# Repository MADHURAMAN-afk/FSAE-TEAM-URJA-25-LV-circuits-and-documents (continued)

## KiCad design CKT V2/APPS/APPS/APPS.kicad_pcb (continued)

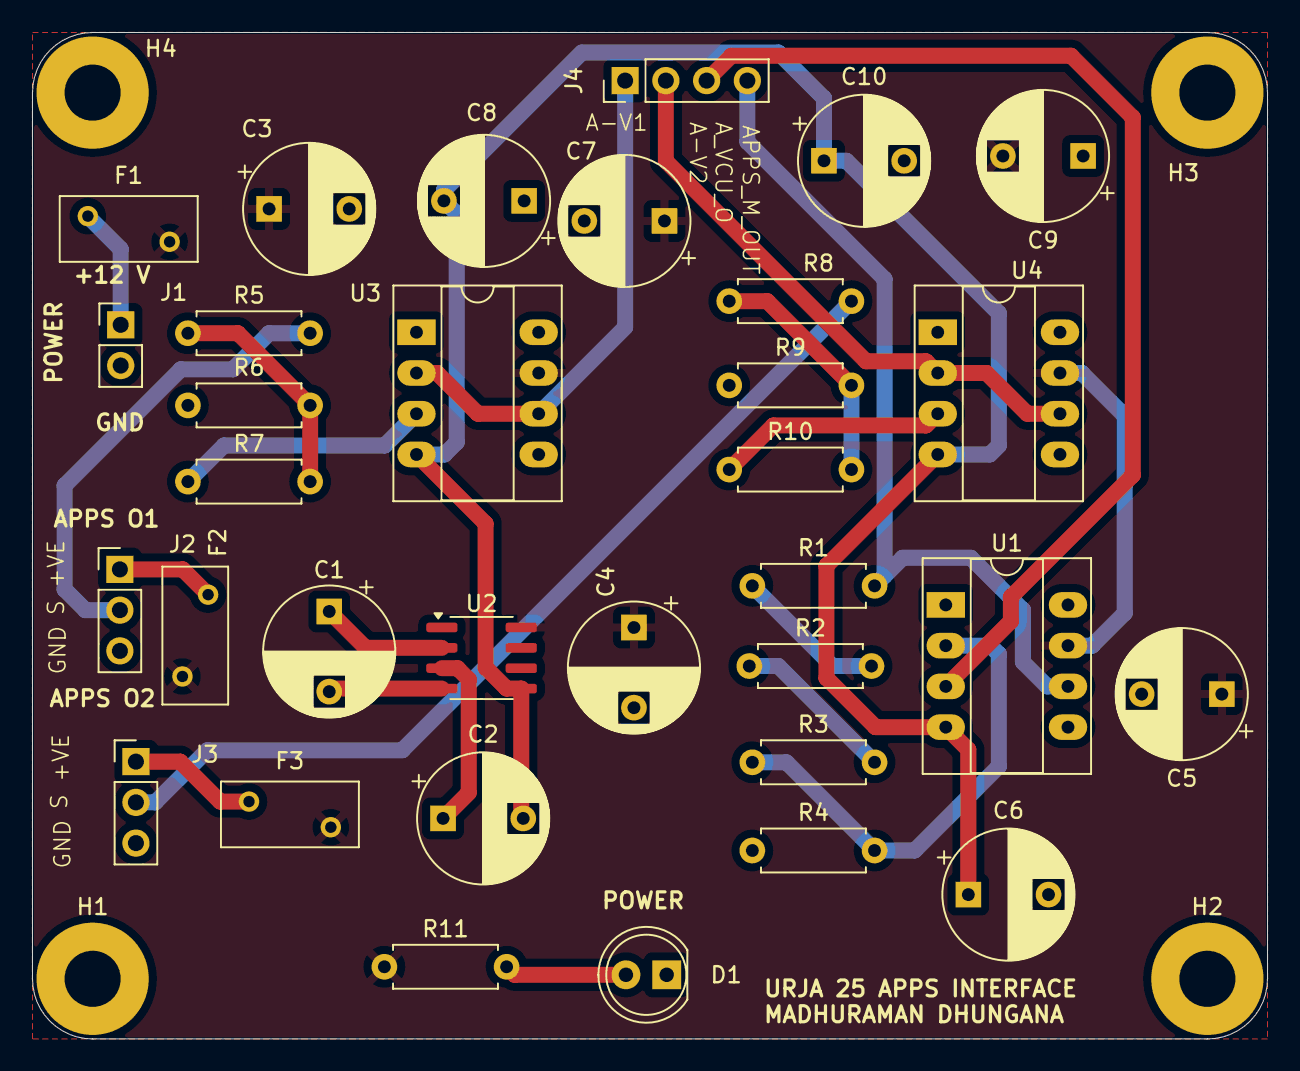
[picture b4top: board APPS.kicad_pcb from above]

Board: 2 copper layers, 77.0 x 62.8 mm, 37 parts (0 on the bottom side), 22 nets.

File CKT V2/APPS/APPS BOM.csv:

Reference,Value,Footprint,Qty
"C1,C2",10uf,Capacitor_THT:CP_Radial_D8.0mm_P5.00mm,2
C3,1uf,Capacitor_THT:CP_Radial_D8.0mm_P5.00mm,1
"C4,C5,C6,C7,C8,C9,C10",0.1uf 25V,Capacitor_THT:CP_Radial_D8.0mm_P5.00mm,7
D1,LED,LED_THT:LED_D5.0mm,1
"F1,F2,F3",25 V 100mA,Fuse:Fuse_BelFuse_0ZRE0008FF_L8.3mm_W3.8mm,3
J1,Conn_01x02_Pin,Connector_PinHeader_2.54mm:PinHeader_1x02_P2.54mm_Vertical,1
"J2,J3",Conn_01x03_Pin,Connector_PinHeader_2.54mm:PinHeader_1x03_P2.54mm_Vertical,2
J4,Conn_01x04_Pin,Connector_PinHeader_2.54mm:PinHeader_1x04_P2.54mm_Vertical,1
"R1,R2",3k3,Resistor_THT:R_Axial_DIN0207_L6.3mm_D2.5mm_P7.62mm_Horizontal,2
R3,100,Resistor_THT:R_Axial_DIN0207_L6.3mm_D2.5mm_P7.62mm_Horizontal,1
"R4,R6,R7,R9,R10",10K,Resistor_THT:R_Axial_DIN0207_L6.3mm_D2.5mm_P7.62mm_Horizontal,5
"R5,R8",27K,Resistor_THT:R_Axial_DIN0207_L6.3mm_D2.5mm_P7.62mm_Horizontal,2
R11,1K,Resistor_THT:R_Axial_DIN0207_L6.3mm_D2.5mm_P7.62mm_Horizontal,1
"U1,U3,U4",LM741,Package_DIP:CERDIP-8_W7.62mm_SideBrazed_LongPads_Socket,3
U2,ICL7660,Package_SO:SOIC-8_3.9x4.9mm_P1.27mm,1

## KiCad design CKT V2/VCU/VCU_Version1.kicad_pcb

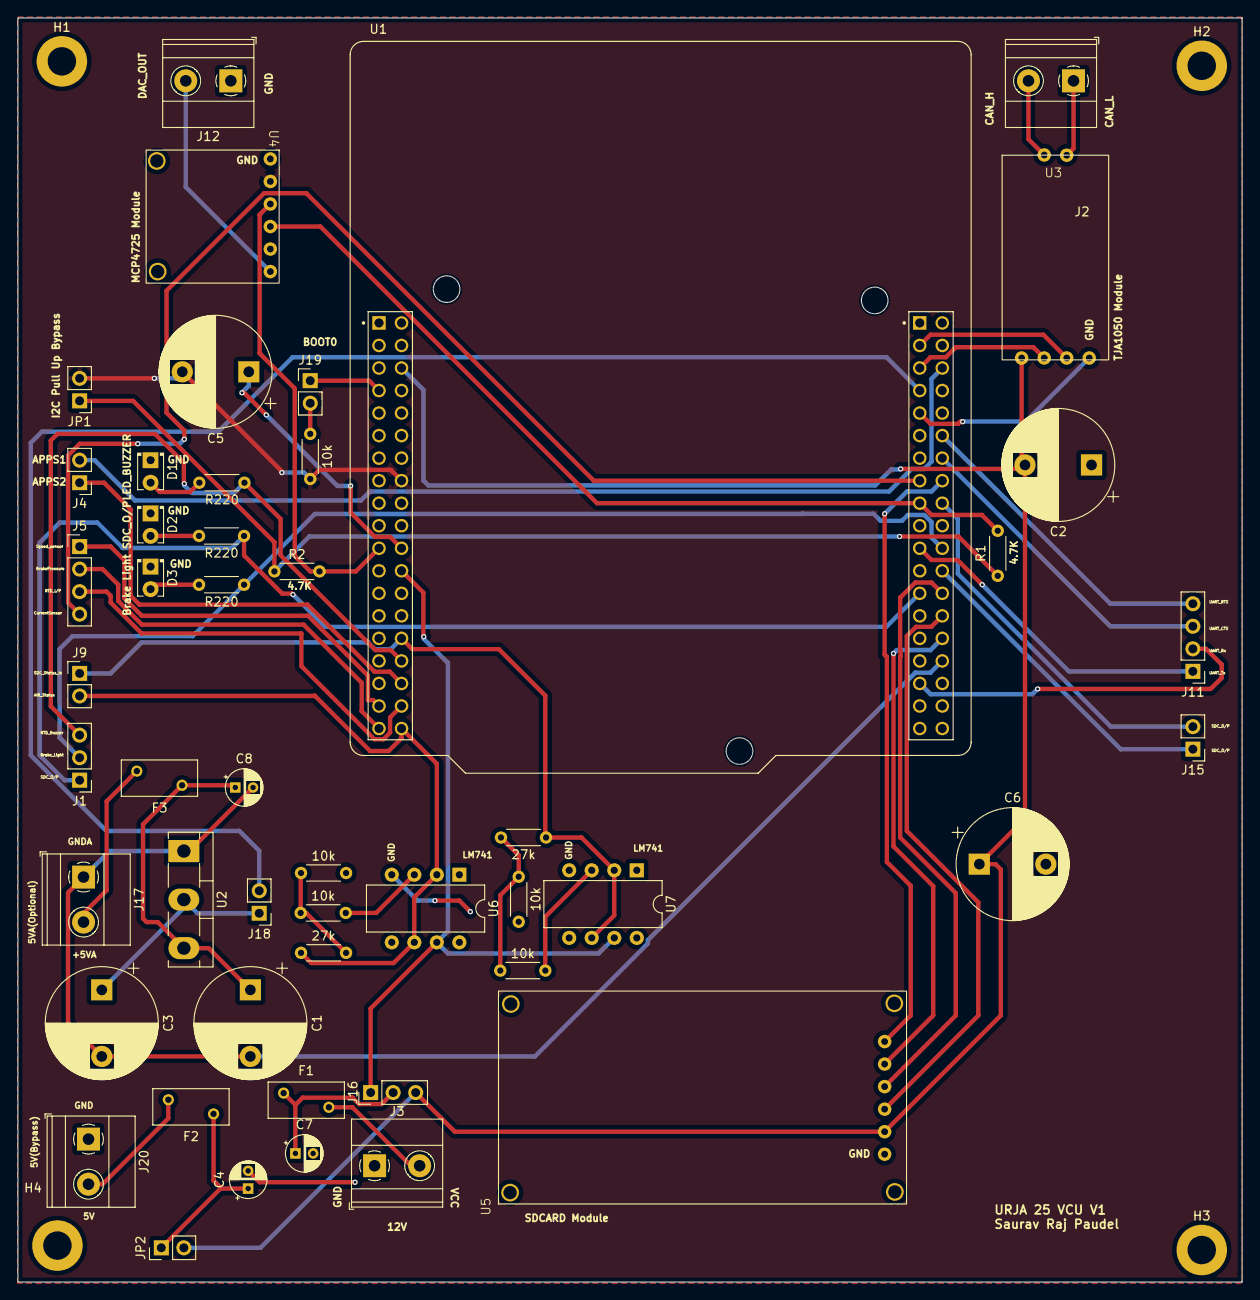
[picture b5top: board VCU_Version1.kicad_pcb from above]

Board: 2 copper layers, 138.0 x 142.5 mm, 53 parts (0 on the bottom side), 51 nets.

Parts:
10k, 10k#2, 10k#3, 10k#4, 10k#5, 27k: R; R_Axial_DIN0204_L3.6mm_D1.6mm_P5.08mm_Horizontal
27k#2: 27k; R_Axial_DIN0204_L3.6mm_D1.6mm_P5.08mm_Horizontal
C1, C3: 10uf; CP_Radial_D12.5mm_P7.50mm
C2, C5, C6: C; CP_Radial_D12.5mm_P7.50mm
C4: 10uf; CP_Radial_D4.0mm_P2.00mm
C7, C8: C; CP_Radial_D4.0mm_P2.00mm
D1, D2, D3: D; LED_D2.0mm_W4.0mm_H2.8mm_FlatTop
F1, F2, F3: Polyfuse; Fuse_BelFuse_0ZRE0005FF_L8.3mm_W3.8mm
H1, H2, H3, H4: MountingHole_Pad; MountingHole_3.2mm_M3_ISO7380_Pad
J1, J16: Conn_01x03_Pin; PinHeader_1x03_P2.54mm_Vertical
J2, J12: Conn_01x02_Pin; TerminalBlock_Phoenix_MKDS-1,5-2-5.08_1x02_P5.08mm_Horizont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
J3, J17, J20: Screw_Terminal_01x02; TerminalBlock_Phoenix_MKDS-1,5-2-5.08_1x02_P5.08mm_Horizont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
J4, J9, J15, J19: Conn_01x02_Pin; PinHeader_1x02_P2.54mm_Vertical
J5, J11: Conn_01x04_Pin; PinHeader_1x04_P2.54mm_Vertical
J18: Analog Voltage Bypass; PinHeader_1x02_P2.54mm_Vertical
JP1, JP2: SolderJumper_2_Open; PinHeader_1x02_P2.54mm_Vertical
R1, R2: 4.7K; R_Axial_DIN0204_L3.6mm_D1.6mm_P5.08mm_Horizontal
R220, R220#2, R220#3: R220; R_Axial_DIN0204_L3.6mm_D1.6mm_P5.08mm_Horizontal
U1: ST_NUCLEO-F410RB
U2: TLV76133DCY; TO-218-3_Vertical
U3: TJA1050_Module
U4: MCP4725
U5: sdcard_module
U6, U7: LM741; CERDIP-8_W7.62mm_SideBrazed

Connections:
3V3: 10k#4.2, C5.2, JP1.2 (B), U1.16 (+3V3), U4.2 (VCC)
5V: C4.1, F2.1, JP2.1 (A)
+3.3VA: J18.2, U1.45 (AVDD)
+5V: C2.2, C6.1, J16.3, JP2.2 (B), U1.6 (E5V), U3.3 (Vcc), U5.2 (VCC)
+5VA: C1.1, C8.1, F3.1, U2.3 (VI)
+12V: J16.1, U1.24 (VIN), U6.7 (V+), U7.7 (V+)
APPS_Sensor1: J4.2, U1.44 (PC5)
APPS_Sensor2: J4.1, U1.34 (PB0)
BOOT0: J19.1, U1.7 (BOOT0)
BrakePressureSensor: J5.2, U1.37 (PC3)
Brake_Light_Digital: J1.2, R220.1, U1.60 (PB2)
CAN_H: J2.2, U3.1 (CAN_H)
CAN_L: J2.1, U3.2 (CAN_L)
CAN_RX: U1.41 (PB8), U3.5 (Rx)
CAN_TX: U1.43 (PB9), U3.4 (Tx)
Current_sensor_BSPD_ANALOG: J5.4, U1.53 (PA7)
DAC_OUT: J12.2, U4.6 (OUT)
Free_GPIO1_AIR_Status: 27k.1, J9.2, U1.38 (PC0), U6.2 (-), U6.6
Free_Output_GPIO1: J15.2, U1.56 (PB11)
Free_Output_GPIO2: J15.1, U1.62 (PB1)
GND: 10k.2, 10k#5.2, C2.1, C4.2, C5.1, C6.2, C7.2, D1.1 (K), D2.1 (K), D3.1 (K), H1.1, H2.1, H3.1, H4.1, J3.1, J12.1, J20.1, U1.22 (GND), U1.47 (GND), U3.6 (GND), U4.1 (GND), U4.5 (GND), U5.1 (GND), U6.4 (V-), U7.4 (V-)
GNDA: C1.2, C3.2, C8.2, J17.1, U1.70 (AGND), U2.1 (GND)
I2C_SCL_N: R1.2, U1.55 (PB6), U4.4 (SCL)
I2C_SDA_P: R2.2, U1.21 (PB7), U4.3 (SDA)
unnamed: D1.2 (A), R220#3.2
unnamed: D2.2 (A), R220#2.2
unnamed: D3.2 (A), R220.2
unnamed: F1.2, J3.2
unnamed: C7.1, F1.1, J16.2
unnamed: F3.2, J17.2
unnamed: C3.1, J18.1, U2.2 (VO)
unnamed: 10k#4.1, J19.2
unnamed: F2.2, J20.2
unnamed: JP1.1 (A), R1.1, R2.1
unnamed: 10k#2.1, 10k#5.1, 27k#2.2
unnamed: 10k.1, 10k#3.1, 27k.2
unnamed: 10k#3.2, U6.3 (+)
unnamed: 10k#2.2, U7.3 (+)
RTD_Buzzer_Digital: J1.3, R220#3.1, U1.32 (PA4)
RTD_DIGITAL_INPUT: J5.3, U1.36 (PC1)
SDC_O/P_DIGITAL: J1.1, R220#2.1, U1.63 (PB10)
SDC_Status_In_VCU: 27k#2.1, J9.1, U1.30 (PA1), U7.2 (-), U7.6
SD_CARD_CLK: U1.68 (PB13), U5.5 (SCK)
SD_CARD_MISO: U1.66 (PB14), U5.3 (MISO)
SD_CARD_MOSI: U1.64 (PB15), U5.4 (MOSI)
SD_CARD_NSS: U1.54 (PB12), U5.6 (CS)
Speed_Sensor_ANALOG_DIGITAL: J5.1, U1.35 (PC2)
UART_CTS: J11.3, U1.52 (PA11)
UART_RTS: J11.4, U1.50 (PA12)
UART_Rx: J11.2, U1.71 (PA10)
UART_Tx: J11.1, U1.59 (PA9)

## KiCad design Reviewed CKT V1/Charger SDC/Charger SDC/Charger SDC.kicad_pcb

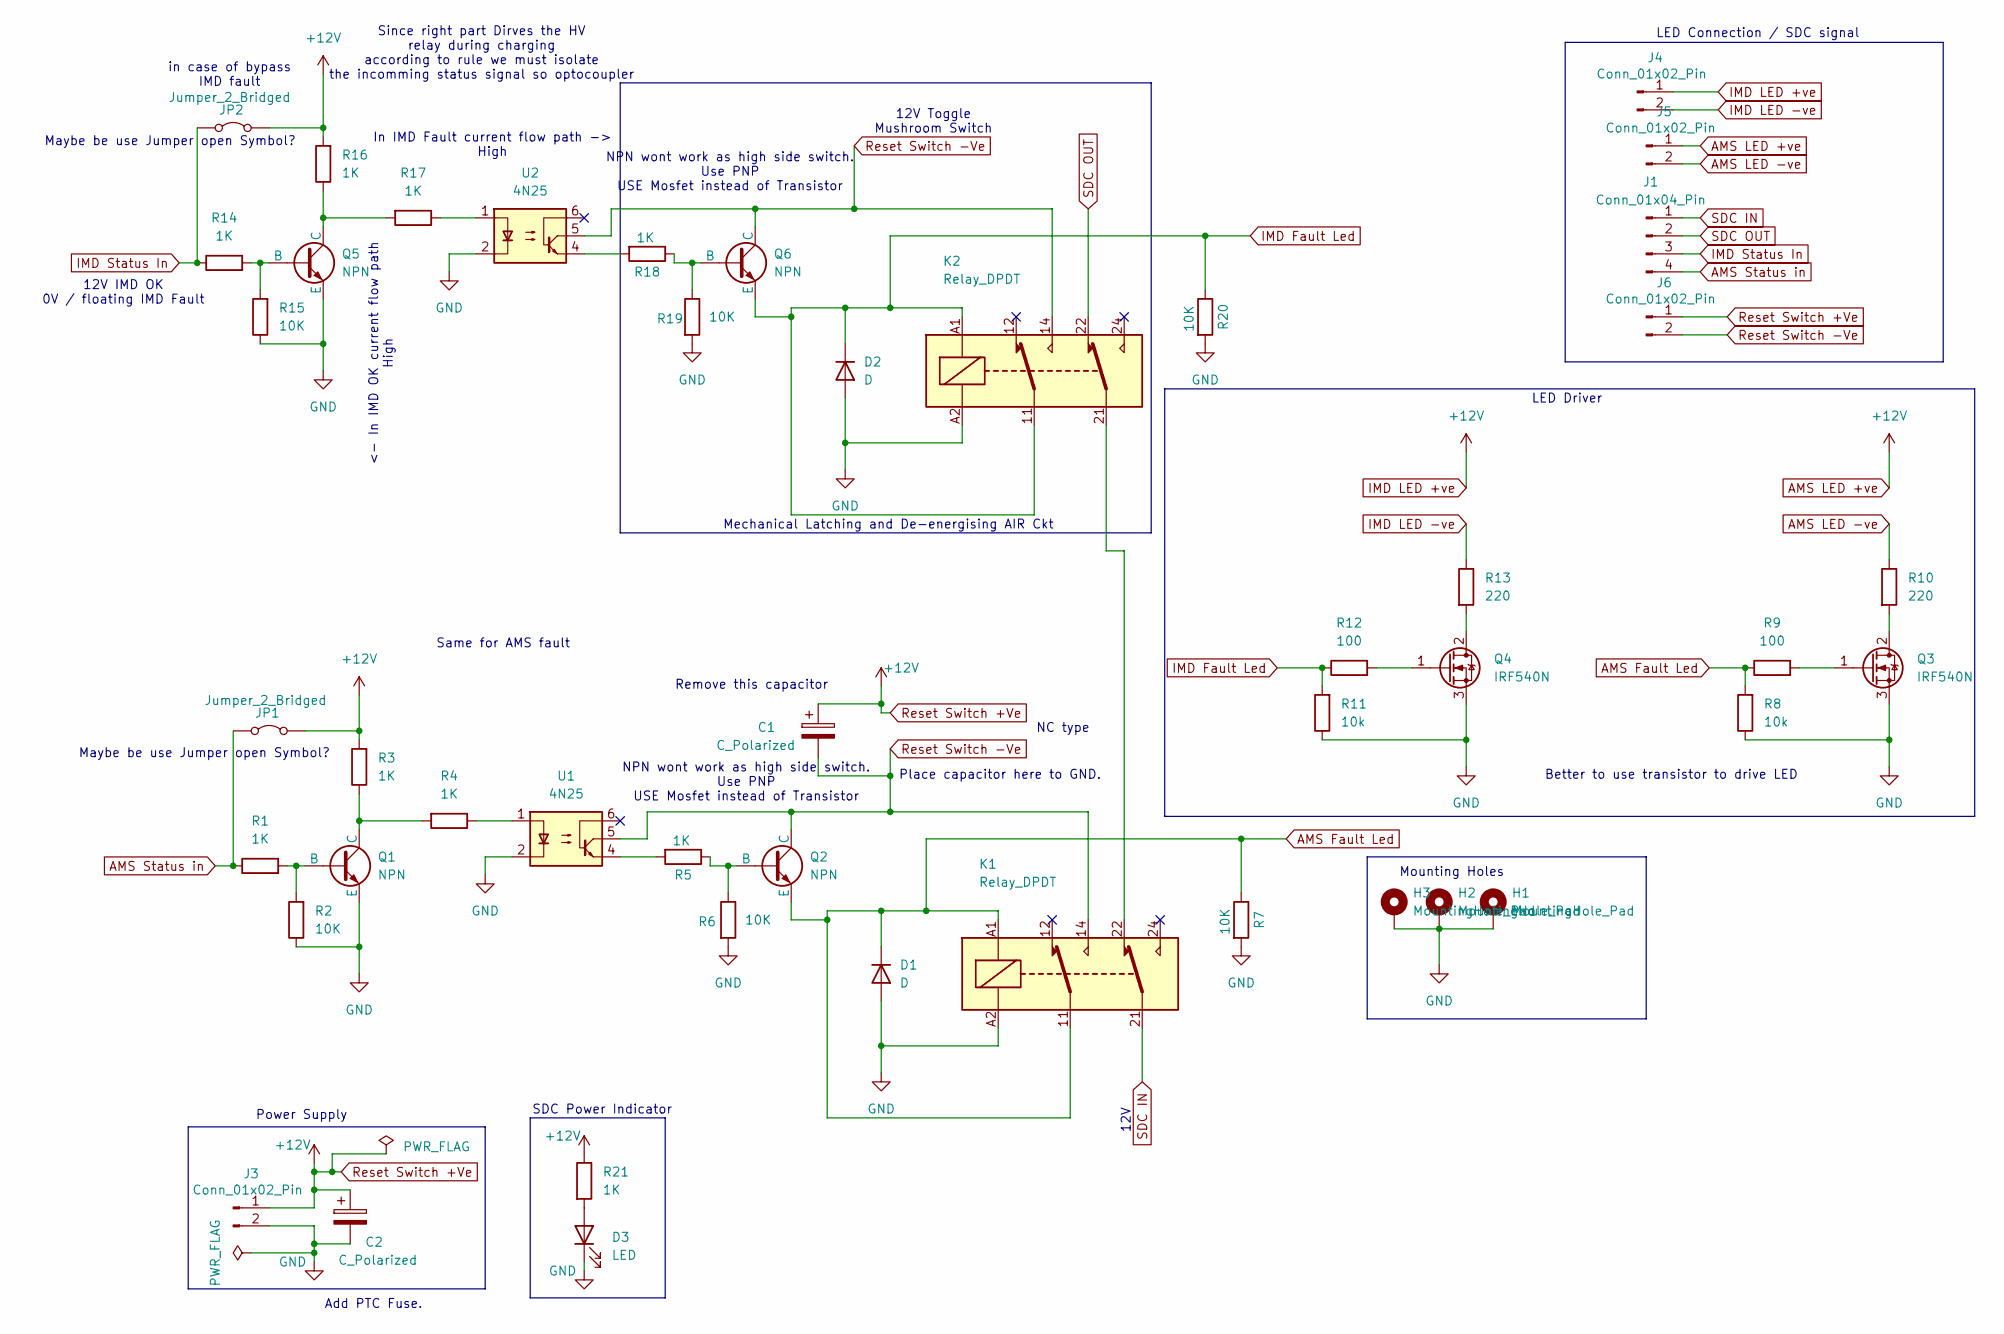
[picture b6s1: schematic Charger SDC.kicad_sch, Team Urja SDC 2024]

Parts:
C1, C2: C_Polarized; CP_Radial_D12.5mm_P7.50mm
D1, D2: D; D_A-405_P7.62mm_Horizontal
D3: LED; LED_D5.0mm
H1, H2, H3: MountingHole_Pad; MountingHole_3.2mm_M3_DIN965_Pad
J1: Conn_01x04_Pin; PinHeader_1x04_P2.54mm_Vertical
J3, J4, J5, J6: Conn_01x02_Pin; PinHeader_1x02_P2.54mm_Vertical
JP1, JP2: Jumper_2_Bridged; PinHeader_1x02_P2.54mm_Vertical
K1, K2: Relay_DPDT; Relay_DPDT_Finder_40.52
Q1, Q5: NPN; TO-92L_Inline_Wide
Q2, Q6: NPN; TO-92_Inline_Wide
Q3, Q4: IRF540N; TO-220-3_Vertical
R1, R3, R4, R5, R14, R16, R17, R18, R21: 1K; R_Axial_DIN0207_L6.3mm_D2.5mm_P7.62mm_Horizontal
R2, R6, R7, R15, R19, R20: 10K; R_Axial_DIN0207_L6.3mm_D2.5mm_P7.62mm_Horizontal
R8, R11: 10k; R_Axial_DIN0204_L3.6mm_D1.6mm_P7.62mm_Horizontal
R9, R12: 100; R_Axial_DIN0204_L3.6mm_D1.6mm_P7.62mm_Horizontal
R10, R13: 220; R_Axial_DIN0204_L3.6mm_D1.6mm_P7.62mm_Horizontal
U1, U2: 4N25; DIP-6_W7.62mm

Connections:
AMS Fault Led: D1.1 (K), K1.11, K1.A1, Q2.3 (E), R7.1, R8.2, R9.1
AMS LED +ve: C1.1, C2.1, J3.1, J4.1, J5.1, J6.1, JP1.2 (B), JP2.2 (B), R3.2, R16.2, R21.1
AMS LED -ve: J5.2, R10.1
AMS Status in: J1.4, JP1.1 (A), R1.1
GND: C2.2, D1.2 (A), D2.2 (A), D3.1 (K), H1.1, H2.1, H3.1, J3.2, K1.A2, K2.A2, Q1.3 (E), Q3.3 (S), Q4.3 (S), Q5.3 (E), R2.1, R6.2, R7.2, R8.1, R11.1, R15.1, R19.2, R20.2, U1.2, U2.2
IMD Fault Led: D2.1 (K), K2.11, K2.A1, Q6.3 (E), R11.2, R12.1, R20.1
IMD LED -ve: J4.2, R13.1
IMD Status In: J1.3, JP2.1 (A), R14.1
unnamed: D3.2 (A), R21.2
unnamed: K1.22, K2.21
unnamed: Q1.2 (B), R1.2, R2.2
unnamed: Q1.1 (C), R3.1, R4.2
unnamed: Q2.2 (B), R5.1, R6.1
unnamed: Q3.2 (D), R10.2
unnamed: Q3.1 (G), R9.2
unnamed: Q4.2 (D), R13.2
unnamed: Q4.1 (G), R12.2
unnamed: Q5.2 (B), R14.2, R15.2
unnamed: Q5.1 (C), R16.1, R17.2
unnamed: Q6.2 (B), R18.1, R19.1
unnamed: R4.1, U1.1
unnamed: R5.2, U1.4
unnamed: R17.1, U2.1
unnamed: R18.2, U2.4
Reset Switch -Ve: C1.2, J6.2, K1.14, K2.14, Q2.1 (C), Q6.1 (C), U1.5, U2.5
SDC IN: J1.1, K1.21
SDC OUT: J1.2, K2.22

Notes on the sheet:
Power Supply
LED Connection / SDC signal
Maybe be use Jumper open Symbol?
LED Driver
Same for AMS fault
Better to use transistor to drive LED
12V Toggle Mushroom Switch
NPN wont work as high side switch. Use PNP USE Mosfet instead of Transistor
in case of bypass IMD fault
Mechanical Latching and De-energising AIR Ckt
In IMD Fault current flow path -> High
Since right part Dirves the HV relay during charging according to rule we must isolate the incomming status signal so optocoupler
Place capacitor here to GND.
NC type
12V IMD OK 0V / floating IMD Fault
Remove this capacitor
Mounting Holes
SDC Power Indicator
Add PTC Fuse.
12V
<- In IMD OK current flow path High

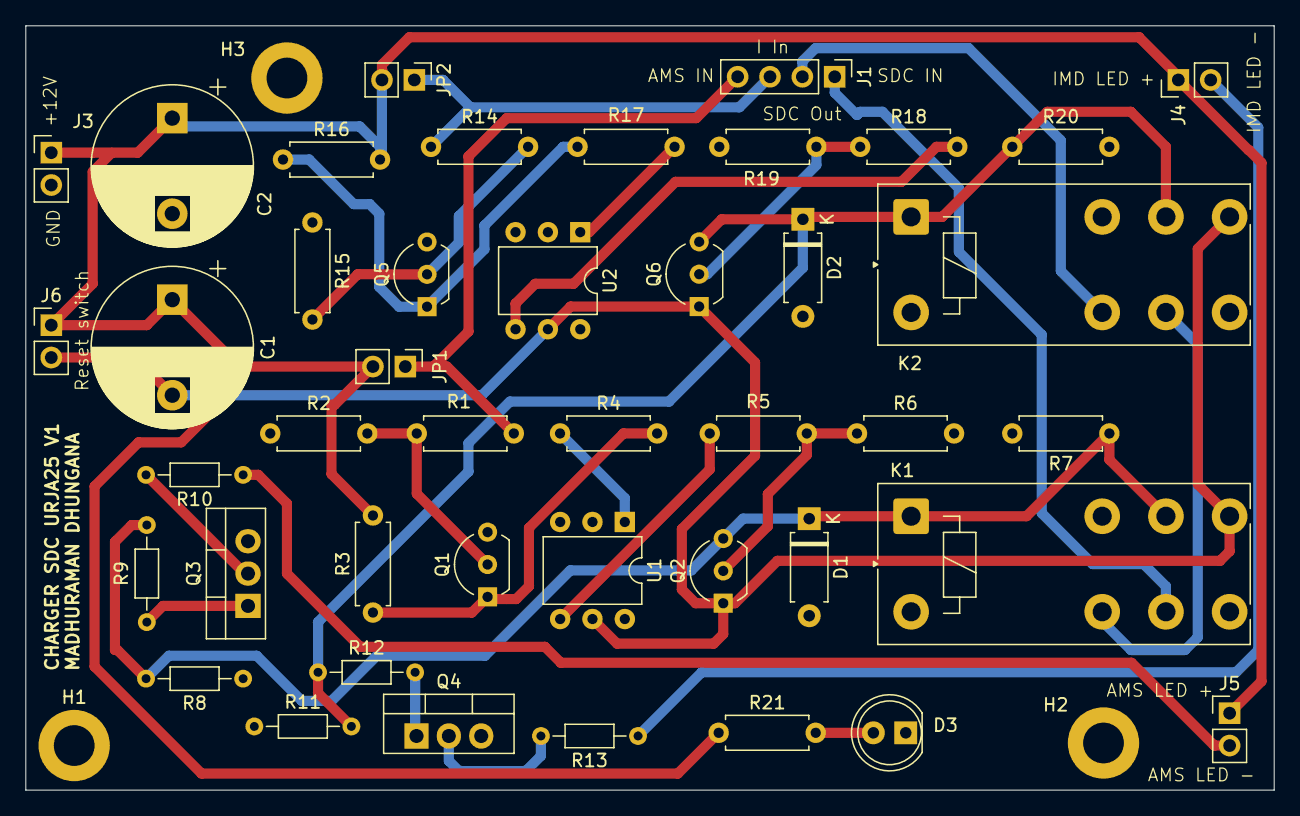
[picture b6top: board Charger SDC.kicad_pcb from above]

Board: 2 copper layers, 98.0 x 60.0 mm, 46 parts (0 on the bottom side), 27 nets.

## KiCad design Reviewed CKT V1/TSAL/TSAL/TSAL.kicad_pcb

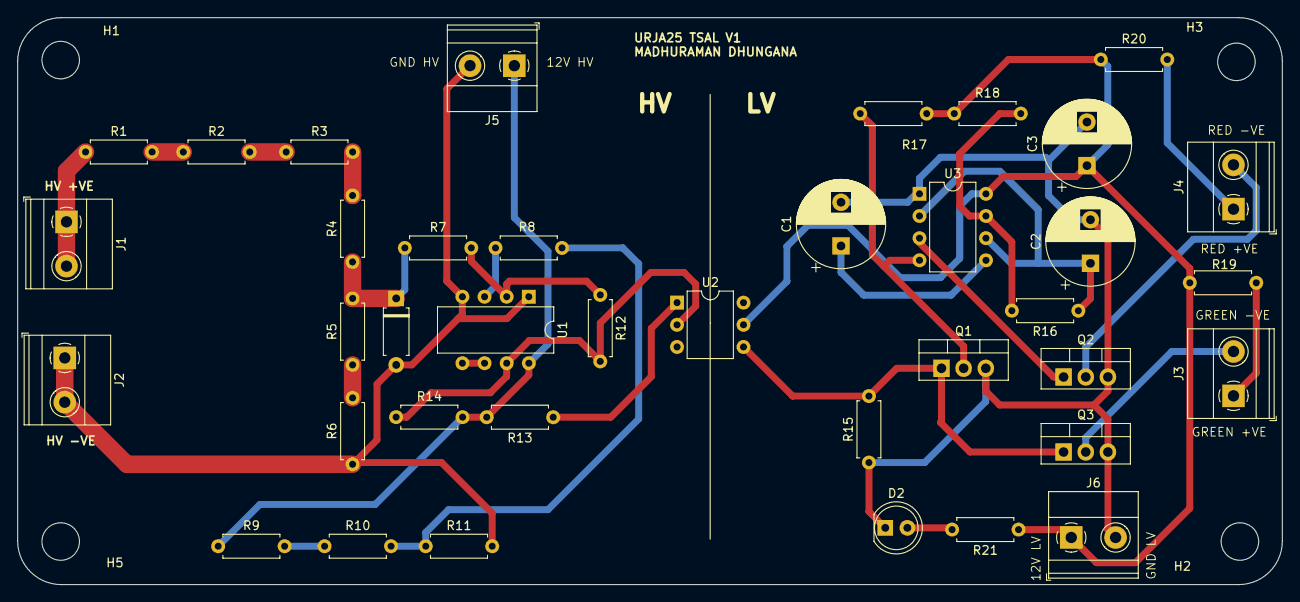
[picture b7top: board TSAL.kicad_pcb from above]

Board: 2 copper layers, 145.0 x 65.0 mm, 42 parts (0 on the bottom side), 28 nets.

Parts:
C1: 100nf; CP_Radial_D10.0mm_P5.00mm
C2: 1uF; CP_Radial_D10.0mm_P5.00mm
C3: 100nF; CP_Radial_D10.0mm_P5.00mm
D1: 12V; D_A-405_P7.62mm_Horizontal
D2: LED; LED_D5.0mm
H1, H2, H3, H5: MountingHole; MountingHole_4.3mm_M4
J1, J2, J3, J4, J5, J6: Conn_01x02_Pin; TerminalBlock_Phoenix_MKDS-1,5-2-5.08_1x02_P5.08mm_Horizont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
Q1, Q2, Q3: IRLZ44N; TO-220-3_Vertical
R1, R2, R3, R4: 249K; R_Axial_DIN0207_L6.3mm_D2.5mm_P7.62mm_Horizontal
R5, R6: 49K9; R_Axial_DIN0207_L6.3mm_D2.5mm_P7.62mm_Horizontal
R7, R19, R20: 100; R_Axial_DIN0207_L6.3mm_D2.5mm_P7.62mm_Horizontal
R8, R14, R15, R17: 10K; R_Axial_DIN0207_L6.3mm_D2.5mm_P7.62mm_Horizontal
R9: 75K; R_Axial_DIN0207_L6.3mm_D2.5mm_P7.62mm_Horizontal
R10: 24K; R_Axial_DIN0207_L6.3mm_D2.5mm_P7.62mm_Horizontal
R11: 900; R_Axial_DIN0207_L6.3mm_D2.5mm_P7.62mm_Horizontal
R12: 1M; R_Axial_DIN0207_L6.3mm_D2.5mm_P7.62mm_Horizontal
R13: 2k2; R_Axial_DIN0207_L6.3mm_D2.5mm_P7.62mm_Horizontal
R16: 220K; R_Axial_DIN0207_L6.3mm_D2.5mm_P7.62mm_Horizontal
R18: 22K; R_Axial_DIN0207_L6.3mm_D2.5mm_P7.62mm_Horizontal
R21: 1K; R_Axial_DIN0207_L6.3mm_D2.5mm_P7.62mm_Horizontal
U1: LM311; CERDIP-8_W7.62mm_SideBrazed
U2: 4N35; DIP-6_W7.62mm
U3: NE555P; DIP-8_W7.62mm

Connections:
+12V: J5.1, R9.1, R13.2, R14.2, U1.8 (V+)
+12VA: C3.1, J6.1, R17.1, R18.1, R19.1, R20.1, R21.1, U2.5, U3.8 (VCC)
/Green LED +Ve: J3.1, R19.2
/Green LED -Ve: J3.2, Q3.2 (D)
/RED LED +VE: J4.1, R20.2
/RED LED -VE: J4.2, Q2.2 (D)
GND1: C1.2, C2.2, C3.2, D2.1 (K), J6.2, Q1.3 (S), Q2.3 (S), Q3.3 (S), R15.1, U3.1 (GND)
HV +VE: J1.1, J1.2, R1.1
HV -VE: D1.2 (A), J2.1, J2.2, J5.2, R6.1, R11.2, U1.1 (GND), U1.4 (V-)
unnamed: D1.1 (K), R4.1, R5.2, R7.1
unnamed: D2.2 (A), R21.2
unnamed: Q1.2 (D), R17.2, U3.4 (R)
unnamed: Q1.1 (G), Q3.1 (G), R15.2, U2.4
unnamed: Q2.1 (G), U3.3 (Q)
unnamed: R1.2, R2.1
unnamed: R2.2, R3.1
unnamed: R3.2, R4.2
unnamed: R5.1, R6.2
unnamed: R9.2, R10.1
unnamed: R8.1, R10.2, R11.1
unnamed: R12.2, R14.1, U1.7, U2.2
unnamed: R13.1, U2.1
unnamed: R7.2, R12.1, U1.2 (+)
unnamed: R8.2, U1.3 (-)
unnamed: U1.5 (BAL), U1.6 (STRB)
unnamed: C1.1, U3.5 (CV)
unnamed: R16.2, R18.2, U3.7 (DIS)
unnamed: C2.1, R16.1, U3.2 (TR), U3.6 (THR)

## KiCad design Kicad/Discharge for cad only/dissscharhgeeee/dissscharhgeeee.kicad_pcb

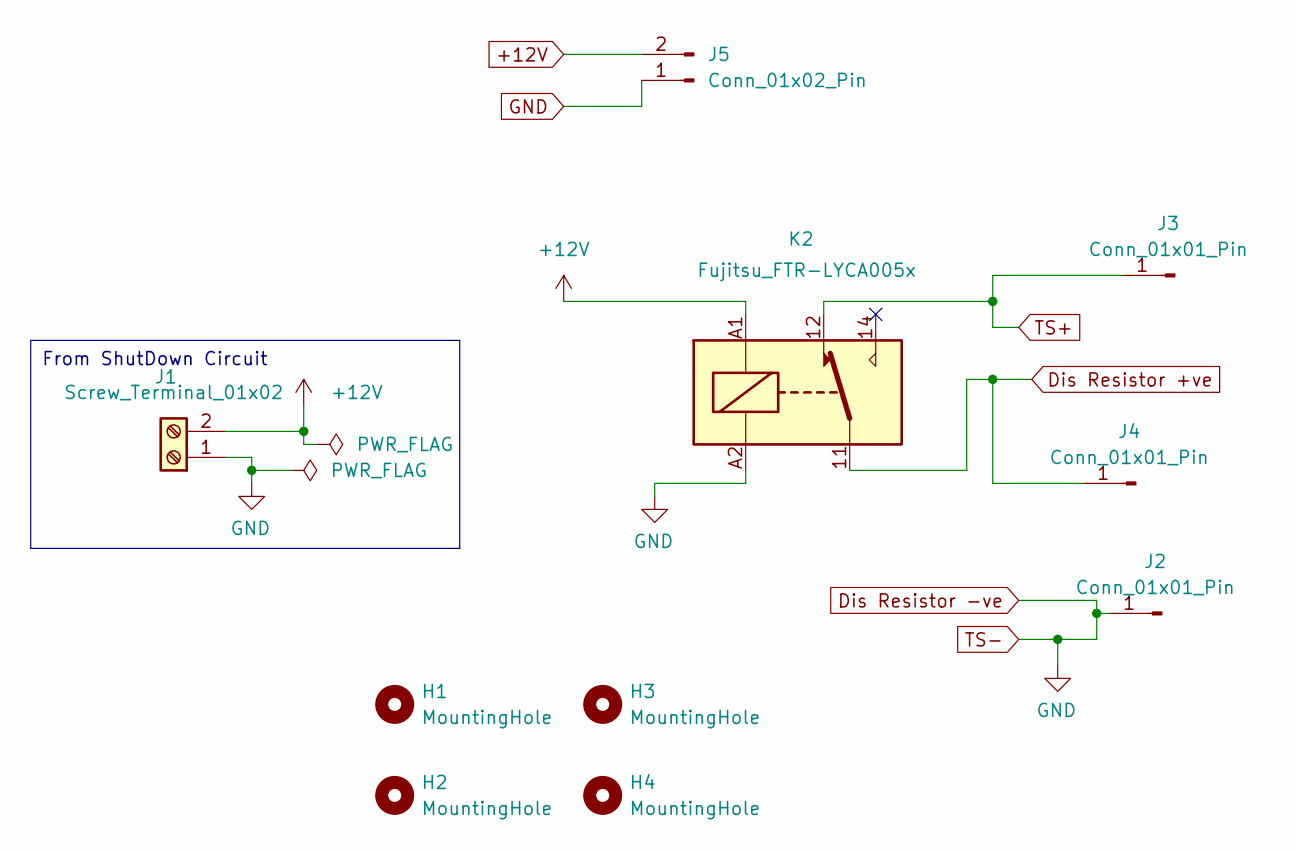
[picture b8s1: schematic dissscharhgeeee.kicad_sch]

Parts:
H1, H2, H3, H4: MountingHole; MountingHole_4.3mm_M4
J1: Screw_Terminal_01x02; TerminalBlock_Phoenix_MKDS-1,5-2-5.08_1x02_P5.08mm_Horizont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
J2, J3, J4: Conn_01x01_Pin; TerminalBlock_Phoenix_MKDS-1,5-2-5.08_1x02_P5.08mm_Horizont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
J5: Conn_01x02_Pin; TerminalBlock_Phoenix_MKDS-1,5-2-5.08_1x02_P5.08mm_Horizont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
K2: Fujitsu_FTR-LYCA005x; Relay_SPDT_Hongfa_HF3F-L-xx-1ZL1T

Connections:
+12V: J1.2, J5.2, K2.A1
Dis Resistor +ve: J4.1, K2.11
Dis Resistor -ve: J1.1, J2.1, J5.1, K2.A2
TS+: J3.1, K2.12

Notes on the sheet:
From ShutDown Circuit

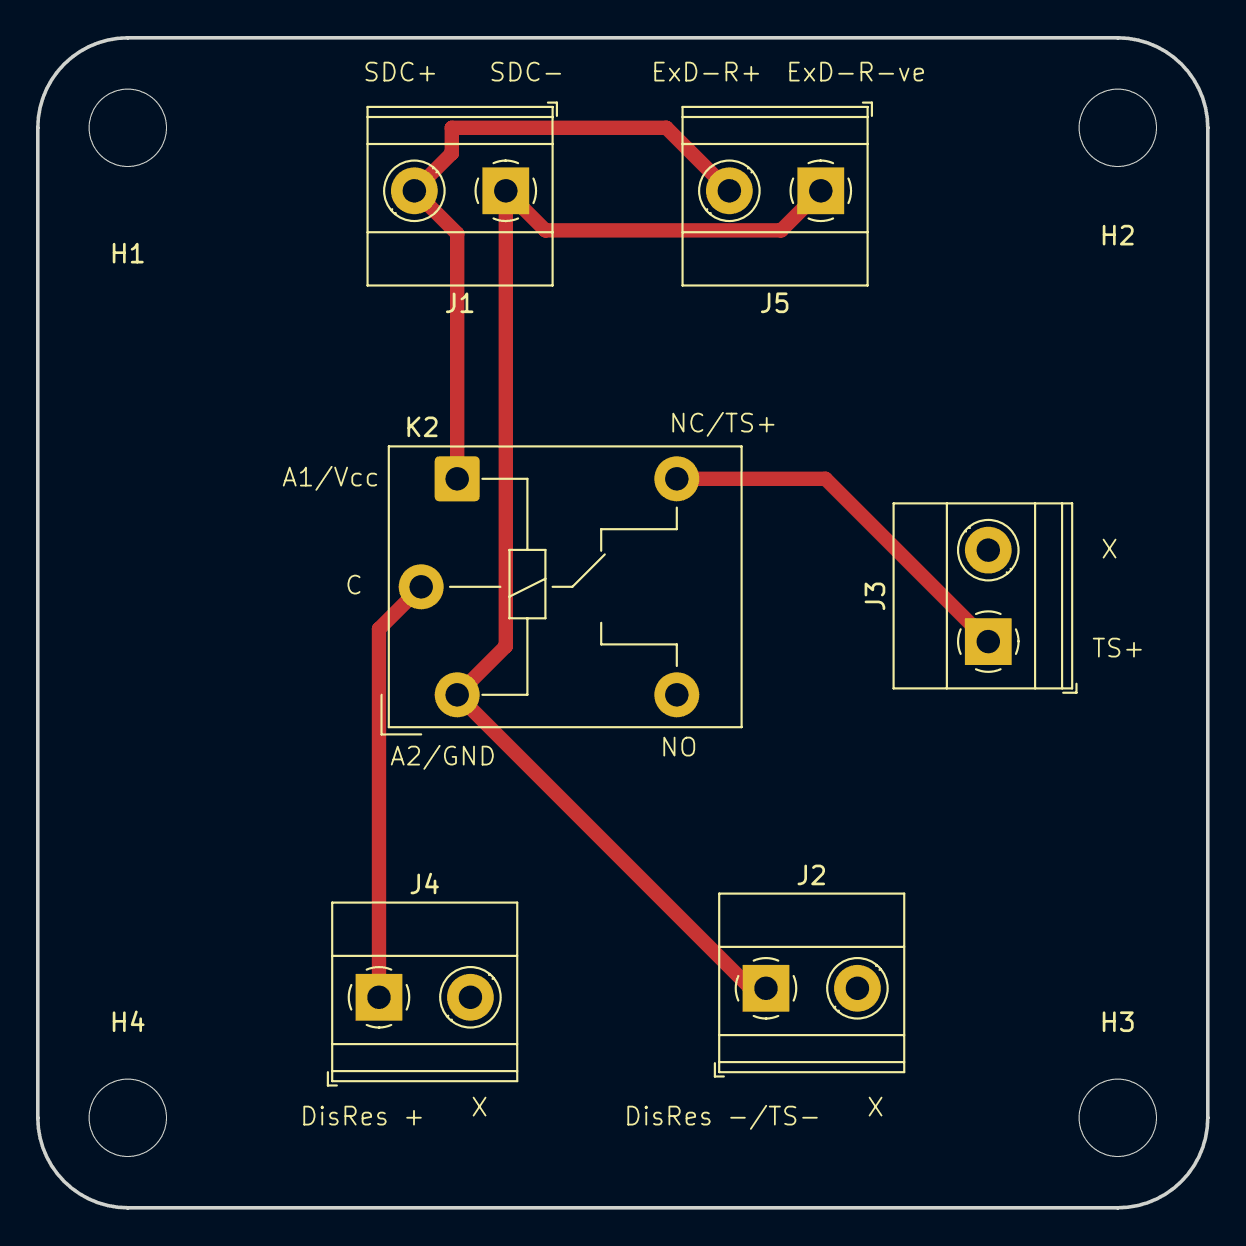
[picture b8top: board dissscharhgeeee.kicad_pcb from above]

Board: 2 copper layers, 65.0 x 65.0 mm, 10 parts (0 on the bottom side), 4 nets.

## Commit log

2025-02-09 Track large files with Git LFS
